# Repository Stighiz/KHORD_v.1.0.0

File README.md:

# KHORD_v.1.0.0
KHORD è una tastiera stenografica digitale open-source, a basso costo e personalizzabile, pensata per studenti, scrittori, programmatori e hobbisti, oltre che per professionisti.

Progettata da zero, include un hardware ottimizzato per la stenografia a due mani e un firmware in C per il microcontrollore ESP32-S3, il quale non è supportato dai firmware open-source esistenti (es. QMK).

La repository è organizzata in 4 cartelle:  
- `Hardware/`: schema elettrico, layout PCB, modello 3D del case, file Gerber  
- `Software/`: firmware in C (ESP-IDF) per gestione matrice, debouncing, protocollo GeminiPR, comunicazione USB con Plover 4.0.1
- `Case/`: file per la stampa 3D del case 
- `Documentazione/`: presentazione di KHORD + relazione tecnica con descrizione dettagliata dell'intero progetto e appendici sull'organizzazione dei file hardware e software, sui i metodi principali contenuti e sulle loro funzioni. 

A [questo link](https://www.typination.com/ploversteno) è disponibie un dizionario da inglese a steno, utile per imparare gli accordi stenografici.

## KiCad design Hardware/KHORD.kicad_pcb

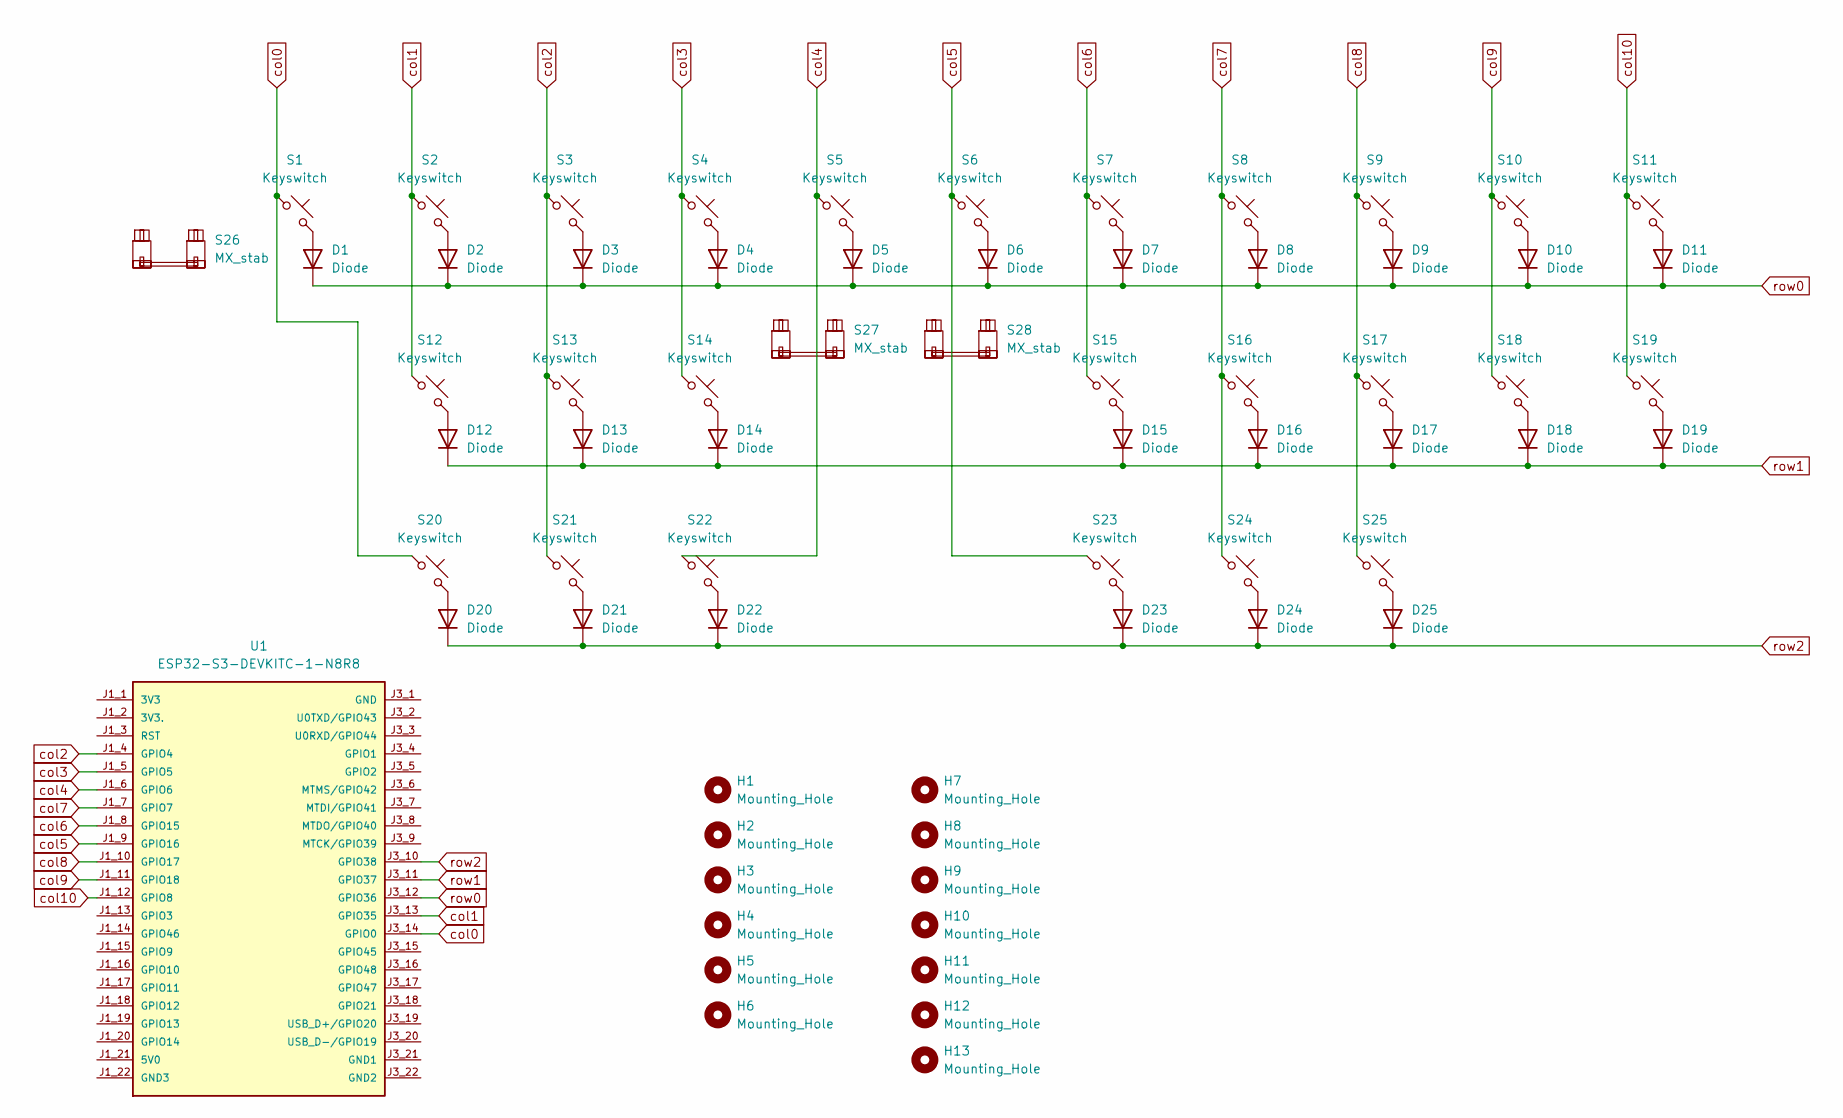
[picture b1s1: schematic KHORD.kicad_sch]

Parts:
D1, D2, D3, D4, D5, D6, D7, D8, D9, D10, D11, D12, D13, D14, D15, D16, D17, D18, D19, D20, D21, D22, D23, D24, D25: Diode; Diode_DO-35
H1, H2, H3, H4, H5, H6, H7, H8, H9, H10, H11, H12, H13: Mounting_Hole; MountingHole_2.2mm_M2
S1, S5, S6: Keyswitch; MX_PCB_2.00u
S2, S3, S4, S7, S8, S9, S10, S11, S12, S13, S14, S15, S16, S17, S18, S19, S20, S21, S22, S23, S24, S25: Keyswitch; MX_PCB_1.00u
S26, S27, S28: MX_stab; STAB_MX_2u
U1: ESP32-S3-DEVKITC-1-N8R8; ESP32-S3-DEVKITC-1-N8R8_largePad

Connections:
unnamed: D1.2 (A), S1.2
unnamed: D2.2 (A), S2.2
unnamed: D3.2 (A), S3.2
unnamed: D4.2 (A), S4.2
unnamed: D5.2 (A), S5.2
unnamed: D6.2 (A), S6.2
unnamed: D7.2 (A), S7.2
unnamed: D8.2 (A), S8.2
unnamed: D9.2 (A), S9.2
unnamed: D10.2 (A), S10.2
unnamed: D11.2 (A), S11.2
unnamed: D12.2 (A), S12.2
unnamed: D13.2 (A), S13.2
unnamed: D14.2 (A), S14.2
unnamed: D15.2 (A), S15.2
unnamed: D16.2 (A), S16.2
unnamed: D17.2 (A), S17.2
unnamed: D18.2 (A), S18.2
unnamed: D19.2 (A), S19.2
unnamed: D20.2 (A), S20.2
unnamed: D21.2 (A), S21.2
unnamed: D22.2 (A), S22.2
unnamed: D23.2 (A), S23.2
unnamed: D24.2 (A), S24.2
unnamed: D25.2 (A), S25.2
col0: S1.1, S20.1, U1.J3_14 (GPIO0)
col1: S2.1, S12.1, U1.J3_13 (GPIO35)
col2: S3.1, S13.1, S21.1, U1.J1_4 (GPIO4)
col3: S4.1, S14.1, U1.J1_5 (GPIO5)
col4: S5.1, S22.1, U1.J1_6 (GPIO6)
col5: S6.1, S23.1, U1.J1_9 (GPIO16)
col6: S7.1, S15.1, U1.J1_8 (GPIO15)
col7: S8.1, S16.1, S24.1, U1.J1_7 (GPIO7)
col8: S9.1, S17.1, S25.1, U1.J1_10 (GPIO17)
col9: S10.1, S18.1, U1.J1_11 (GPIO18)
col10: S11.1, S19.1, U1.J1_12 (GPIO8)
row0: D1.1 (K), D2.1 (K), D3.1 (K), D4.1 (K), D5.1 (K), D6.1 (K), D7.1 (K), D8.1 (K), D9.1 (K), D10.1 (K), D11.1 (K), U1.J3_12 (GPIO36)
row1: D12.1 (K), D13.1 (K), D14.1 (K), D15.1 (K), D16.1 (K), D17.1 (K), D18.1 (K), D19.1 (K), U1.J3_11 (GPIO37)
row2: D20.1 (K), D21.1 (K), D22.1 (K), D23.1 (K), D24.1 (K), D25.1 (K), U1.J3_10 (GPIO38)

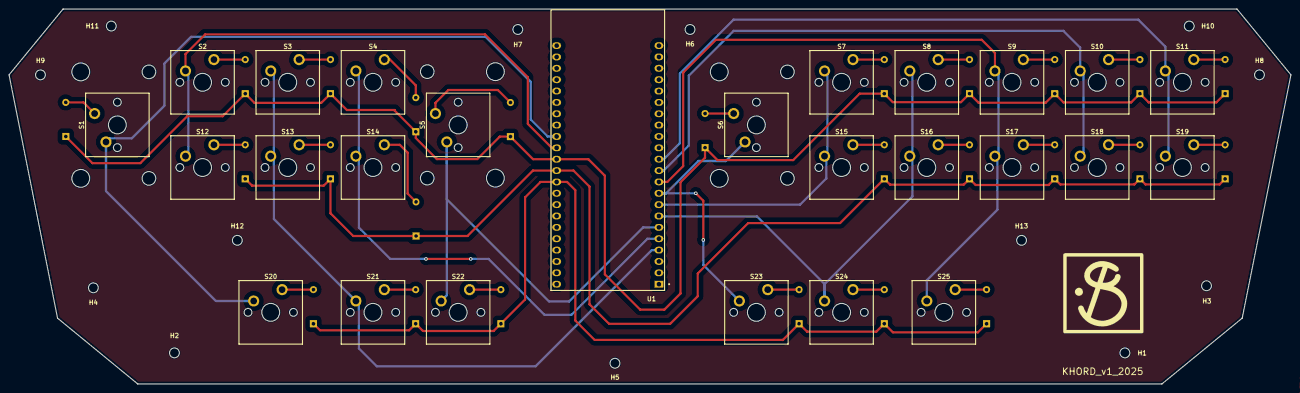
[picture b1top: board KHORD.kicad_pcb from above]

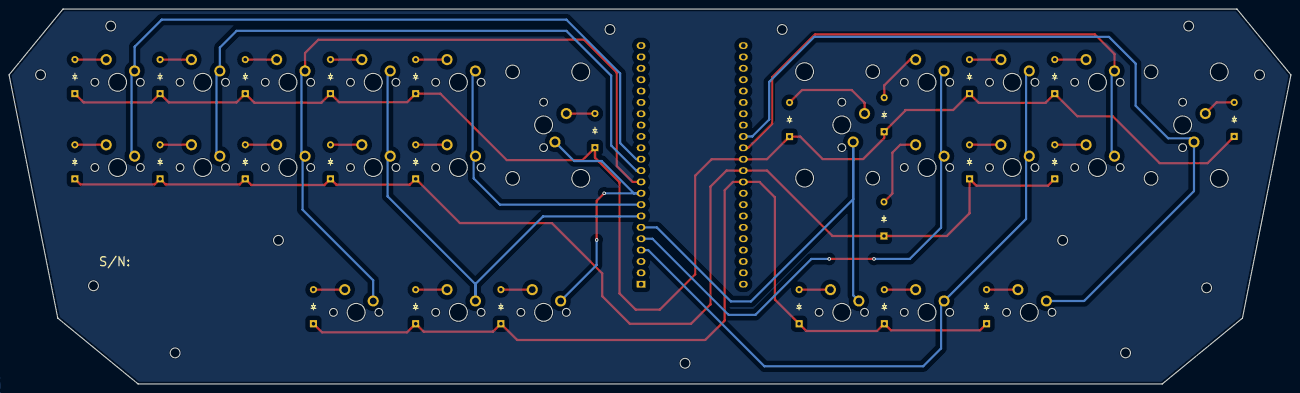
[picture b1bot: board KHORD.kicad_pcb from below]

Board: 2 copper layers, 286.6 x 83.8 mm, 67 parts (25 on the bottom side), 39 nets.

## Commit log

2025-07-30 feat: Added software folder containing KHORD firmware to the project
2025-07-31 feat: Added 3d model for KHORD case
2025-10-17 Fix link formatting in README.md
2025-10-17 Add image to KHORD README
    Added an image of the KHORD keyboard to the README.
